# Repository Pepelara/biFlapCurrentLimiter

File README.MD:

This is bidirectional current limiter.

This is made to limit current for VW recirculation flap motor so it 
doesnt break the gear.

It works by measuring a voltage drop over 2 ohm resistor. When the
voltage drop is too great, it cuts off the motor power supply.

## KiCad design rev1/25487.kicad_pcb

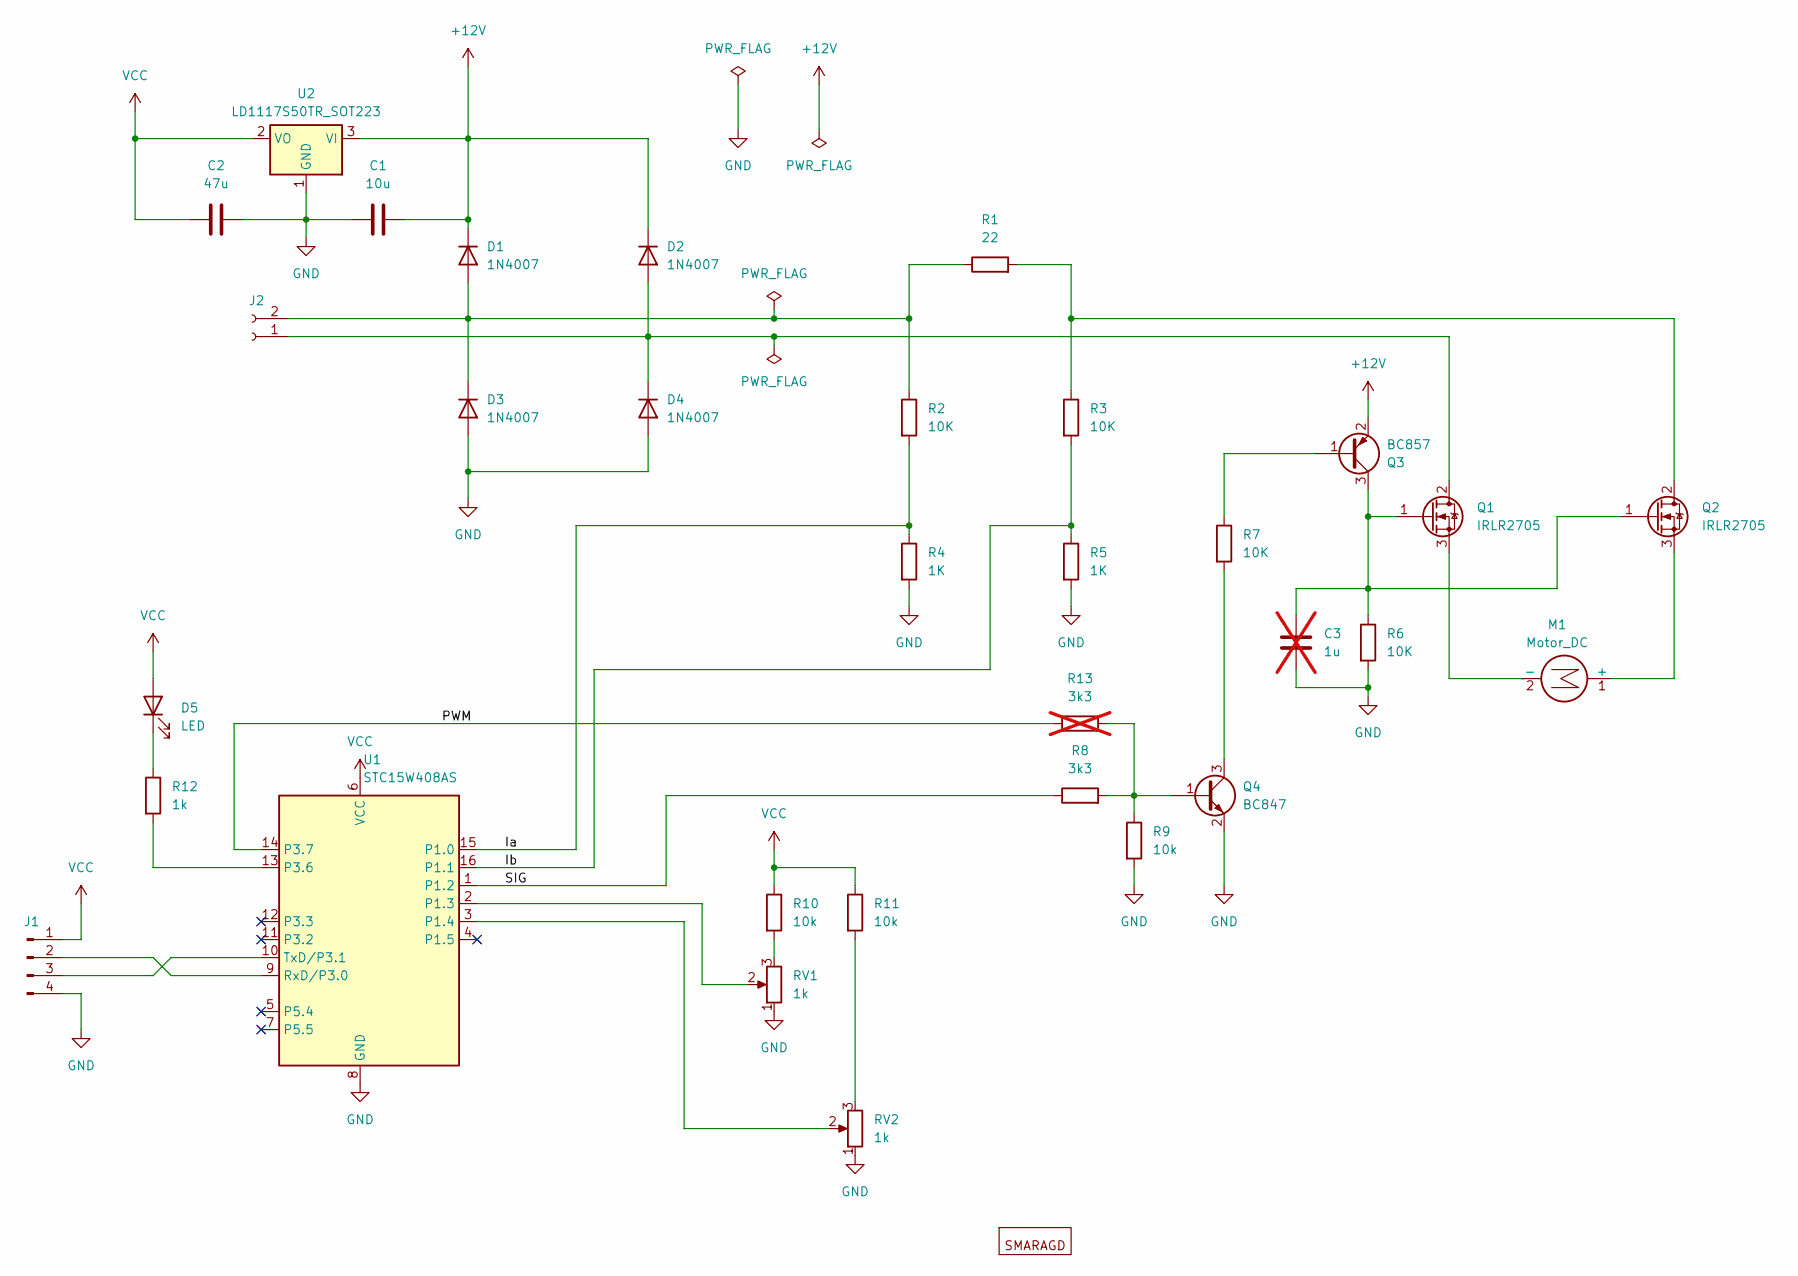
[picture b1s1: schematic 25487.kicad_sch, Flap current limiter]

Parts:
C1: 10u; C_0805_2012Metric
C2: 47u; C_0805_2012Metric
C3: 1u; C_0805_2012Metric; not fitted
D1, D2, D3, D4: 1N4007; D_SOD-323
D5: LED; LED_0805_2012Metric
J1: Conn_01x04_Pin; PinHeader_1x04_P2.54mm_Vertical
J2: Conn_01x02_Socket; TerminalBlock_bornier-2_P5.08mm
M1: Motor_DC; TerminalBlock_bornier-2_P5.08mm
Q1, Q2: IRLR2705; TO-252-2
Q3: BC857; SOT-23-3
Q4: BC847; SOT-23-3
R1: 22; R_1206_3216Metric
R2, R3, R6, R7: 10K; R_0805_2012Metric
R4, R5: 1K; R_0805_2012Metric
R8: 3k3; R_0805_2012Metric
R9, R10, R11: 10k; R_0805_2012Metric
R12: 1k; R_0805_2012Metric
R13: 3k3; R_0805_2012Metric; not fitted
RV1, RV2: 1k; Potentiometer_Bourns_3314J_Vertical
SMARAGD1: SMARAGD_S
U1: STC15W408AS; SOP-16_4.4x10.4mm_P1.27mm
U2: LD1117S50TR_SOT223; SOT-223-3_TabPin2

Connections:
+12V: C1.2, D1.1 (K), D2.1 (K), Q3.2 (E), U2.3 (VI)
/Ia: R2.2, R4.1, U1.15 (P1.0)
/Ib: R3.2, R5.1, U1.16 (P1.1)
/PWM: R13.1, U1.14 (P3.7)
/SIG: R8.1, U1.1 (P1.2)
GND: C1.1, C2.2, C3.1, D3.2 (A), D4.2 (A), J1.4, Q4.2 (E), R4.2, R5.2, R6.2, R9.2, RV1.1, RV2.1, U1.8 (GND), U2.1 (GND)
unnamed: D1.2 (A), D3.1 (K), J2.2, R1.1, R2.1
unnamed: D2.2 (A), D4.1 (K), J2.1, Q1.2 (D)
unnamed: D5.1 (K), R12.1
unnamed: J1.2, U1.9 (RxD/P3.0)
unnamed: J1.3, U1.10 (TxD/P3.1)
unnamed: M1.1 (+), Q2.3 (S)
unnamed: M1.2 (-), Q1.3 (S)
unnamed: C3.2, Q1.1 (G), Q2.1 (G), Q3.3 (C), R6.1
unnamed: Q2.2 (D), R1.2, R3.1
unnamed: Q3.1 (B), R7.1
unnamed: Q4.1 (B), R8.2, R9.1, R13.2
unnamed: Q4.3 (C), R7.2
unnamed: R10.2, RV1.3
unnamed: R11.2, RV2.3
unnamed: RV1.2, U1.2 (P1.3)
unnamed: RV2.2, U1.3 (P1.4)
unnamed: R12.2, U1.13 (P3.6)
VCC: C2.1, D5.2 (A), J1.1, R10.1, R11.1, U1.6 (VCC), U2.2 (VO)

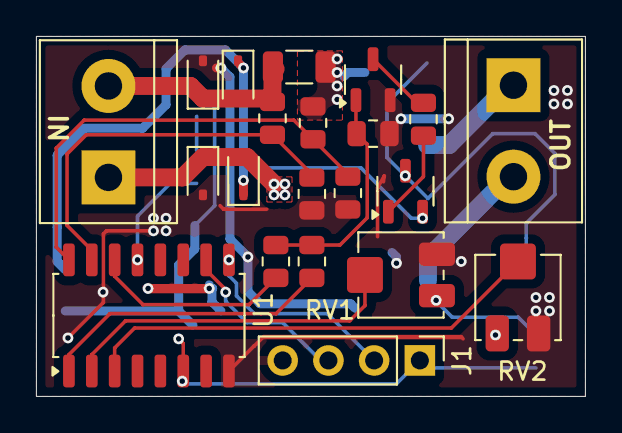
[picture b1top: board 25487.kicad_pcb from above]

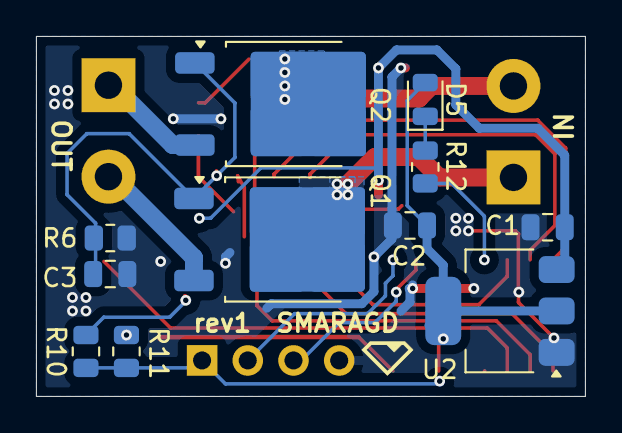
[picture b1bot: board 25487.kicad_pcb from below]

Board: 2 copper layers, 30.5 x 20.0 mm, 33 parts (12 on the bottom side), 24 nets.

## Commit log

2025-07-23 Initial commit. rev1
2025-07-26 Compensated the sense negative voltage
